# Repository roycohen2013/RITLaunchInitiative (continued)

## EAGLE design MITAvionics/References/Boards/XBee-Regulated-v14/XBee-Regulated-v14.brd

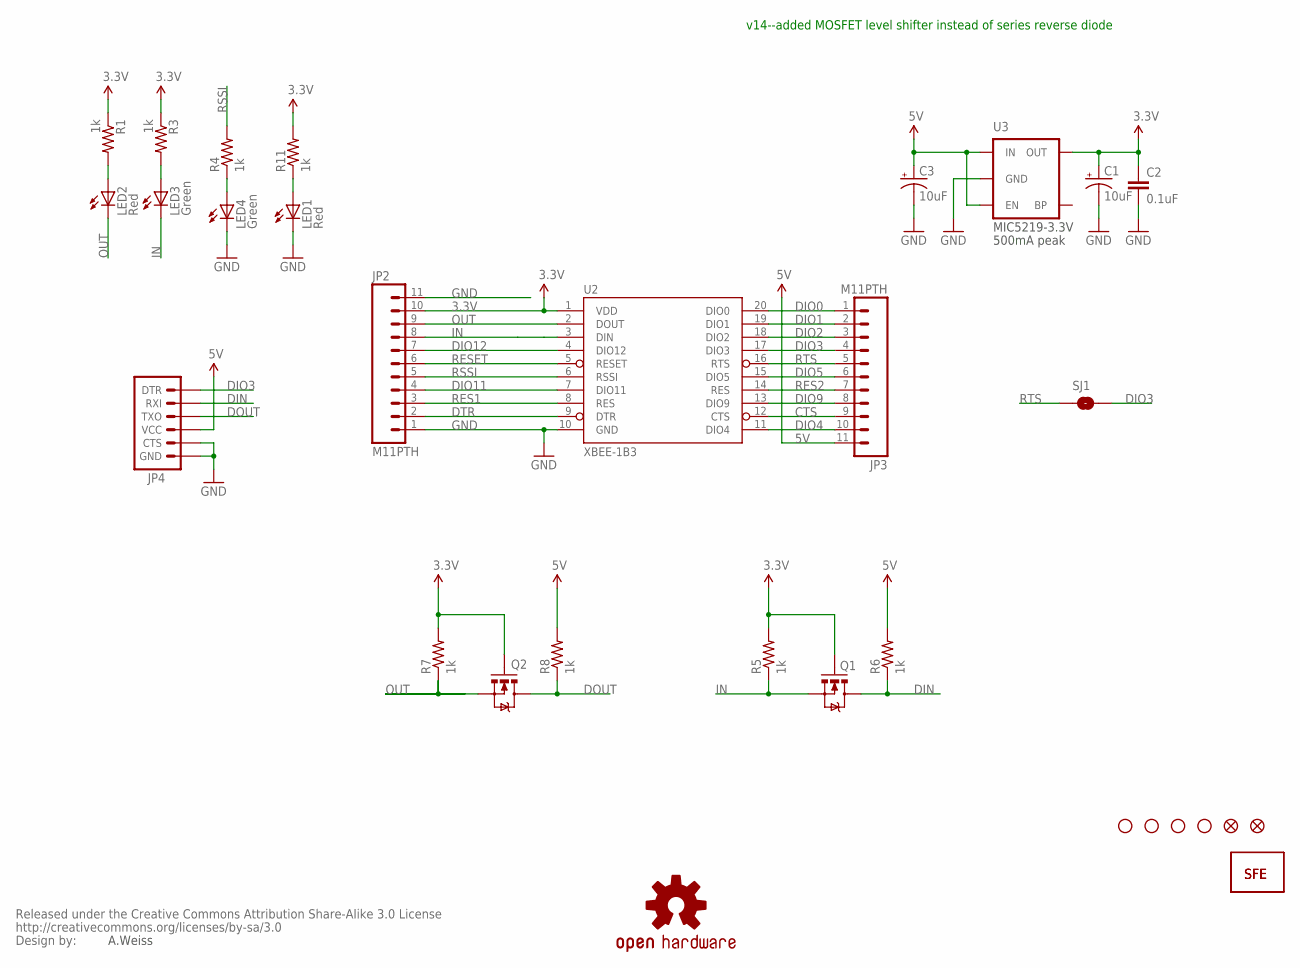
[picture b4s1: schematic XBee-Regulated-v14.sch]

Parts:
C1, C3: 10uF; EIA3216
C2: 0.1uF; 0402-CAP
JP2, JP3: M11PTH; 1X11
JP4: ARDUINO_SERIAL_PROGRAMPTH; 1X06
LED1, LED2: Red; LED-0603
LED3, LED4: Green; LED-0603
Q1, Q2: MOSFET-NCHANNELSMD; SOT23-3
R1, R3, R4, R5, R6, R7, R8, R11: 1k; 0402-RES
SJ1: SOLDERJUMPERNO; SJ_2S-NO
U2: XBEE-1B3; XBEE-SMD
U3: V_REG_LDOSMD; SOT23-5
U$1: LOGO-SFESK; SFE-LOGO-FLAME
U$3: OSHW-LOGOS; OSHW-LOGO-S
U$4: LOGO-SFENEW; SFE-NEW-WEBLOGO
U$5, U$9, U$10, U$11: STAND-OFF
U$7, U$16: FIDUCIAL1X2; FIDUCIAL-1X2
U$8: CREATIVE_COMMONS

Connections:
3.3V: C1.A (+), C2.1, JP2.10, Q1.1 (G), Q2.1 (G), R1.1, R3.1, R5.2, R7.2, R11.2, U2.1 (VDD), U3.5 (OUT)
5V: C3.A (+), JP3.11, JP4.4 (VCC), R6.2, R8.2, U3.1 (IN), U3.3 (EN)
CTS: JP3.9, U2.12 (CTS)
DIN: JP4.2 (RXI), Q1.3 (D), R6.1
DIO0: JP3.1, U2.20 (DIO0)
DIO1: JP3.2, U2.19 (DIO1)
DIO2: JP3.3, U2.18 (DIO2)
DIO3: JP3.4, JP4.1 (DTR), SJ1.2, U2.17 (DIO3)
DIO4: JP3.10, U2.11 (DIO4)
DIO5: JP3.6, U2.15 (DIO5)
DIO9: JP3.8, U2.13 (DIO9)
DIO11: JP2.4, U2.7 (DIO11)
DIO12: JP2.7, U2.4 (DIO12)
DOUT: JP4.3 (TXO), Q2.3 (D), R8.1
DTR: JP2.2, U2.9 (DTR)
GND: C1.C (-), C2.2, C3.C (-), JP2.1, JP2.11, JP4.5 (CTS), JP4.6 (GND), LED1.C, LED4.C, U2.10 (GND), U3.2 (GND)
IN: JP2.8, LED3.C, Q1.2 (S), R5.1, U2.3 (DIN)
unnamed: LED2.A, R1.2
unnamed: LED4.A, R4.1
unnamed: LED3.A, R3.2
unnamed: LED1.A, R11.1
OUT: JP2.9, LED2.C, Q2.2 (S), R7.1, U2.2 (DOUT)
RES1: JP2.3, U2.8 (RES)
RES2: JP3.7, U2.14 (RES)
RESET: JP2.6, U2.5 (RESET)
RSSI: JP2.5, R4.2, U2.6 (RSSI)
RTS: JP3.5, SJ1.1, U2.16 (RTS)

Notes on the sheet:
A.Weiss
v14--added MOSFET level shifter instead of series reverse diode
MIC5219-3.3V
500mA peak

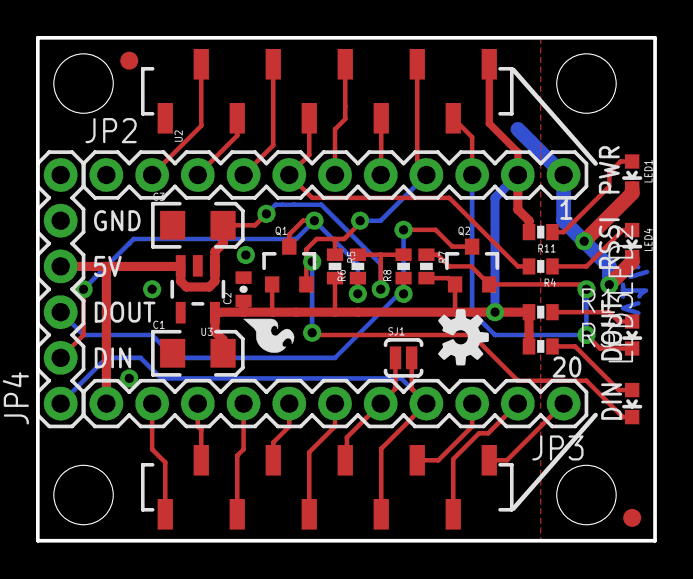
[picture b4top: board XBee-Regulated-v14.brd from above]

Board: 2 copper layers, 34.3 x 27.9 mm, 33 parts (1 on the bottom side), 27 nets.

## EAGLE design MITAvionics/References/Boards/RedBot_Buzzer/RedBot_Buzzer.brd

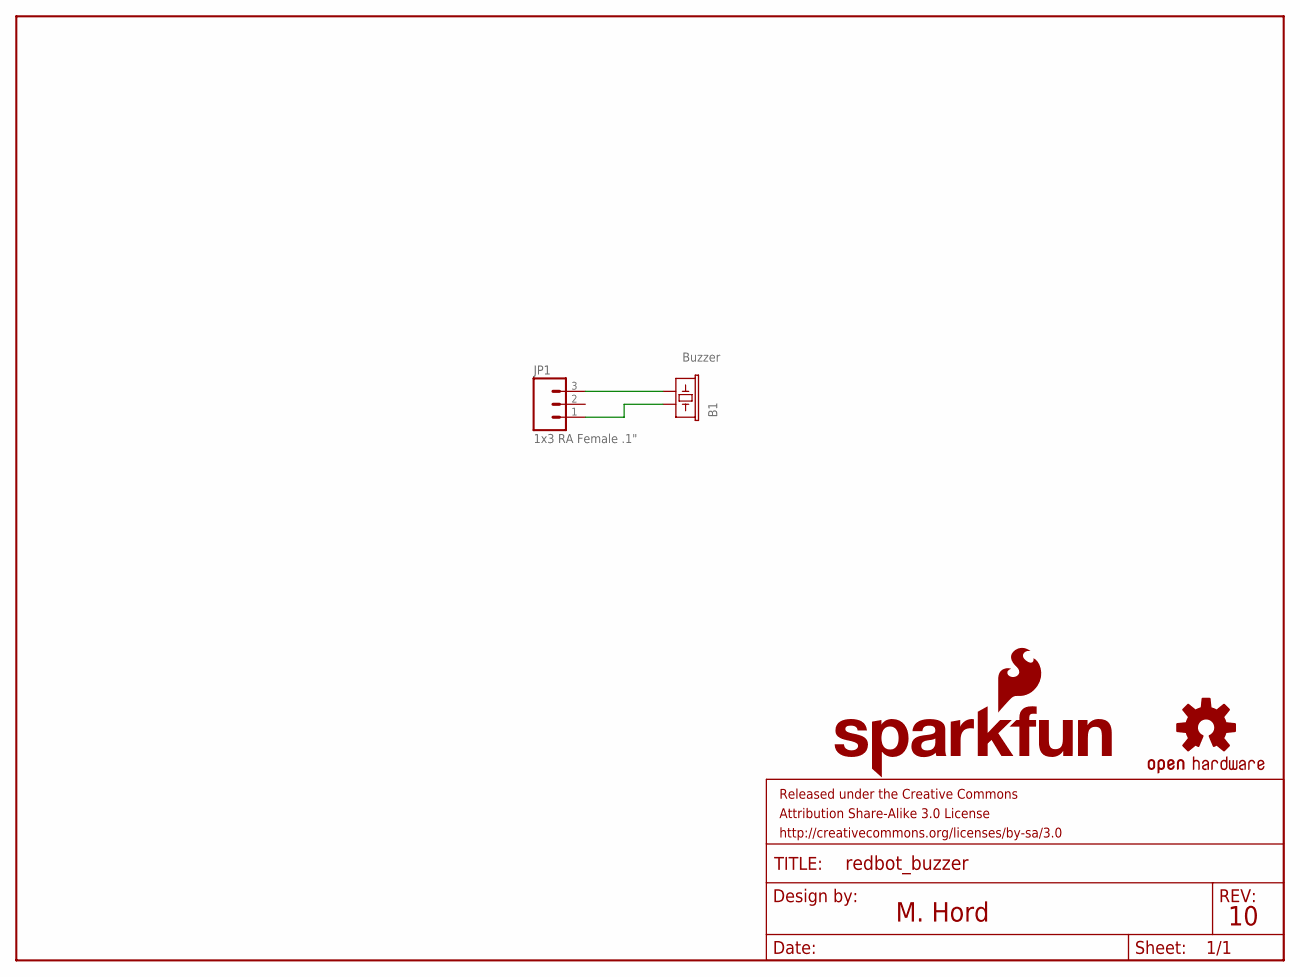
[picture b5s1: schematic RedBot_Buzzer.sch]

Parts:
B1: Buzzer; BUZZER-CCV
FRAME1: FRAME-LETTER; CREATIVE_COMMONS
JP1: 1x3 RA Female .1"; 1X03_SMD_RA_FEMALE
LOGO1: OSHW-LOGOS; OSHW-LOGO-S
LOGO2: SFE_LOGO_NAME_FLAME.1_INCH; SFE_LOGO_NAME_FLAME_.1

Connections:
unnamed: B1.+ (1), JP1.1
unnamed: B1.- (2), JP1.3

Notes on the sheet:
M. Hord

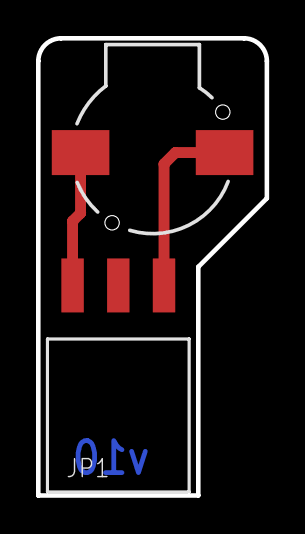
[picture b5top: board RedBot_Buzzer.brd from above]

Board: 2 copper layers, 12.7 x 25.4 mm, 5 parts (2 on the bottom side), 2 nets.

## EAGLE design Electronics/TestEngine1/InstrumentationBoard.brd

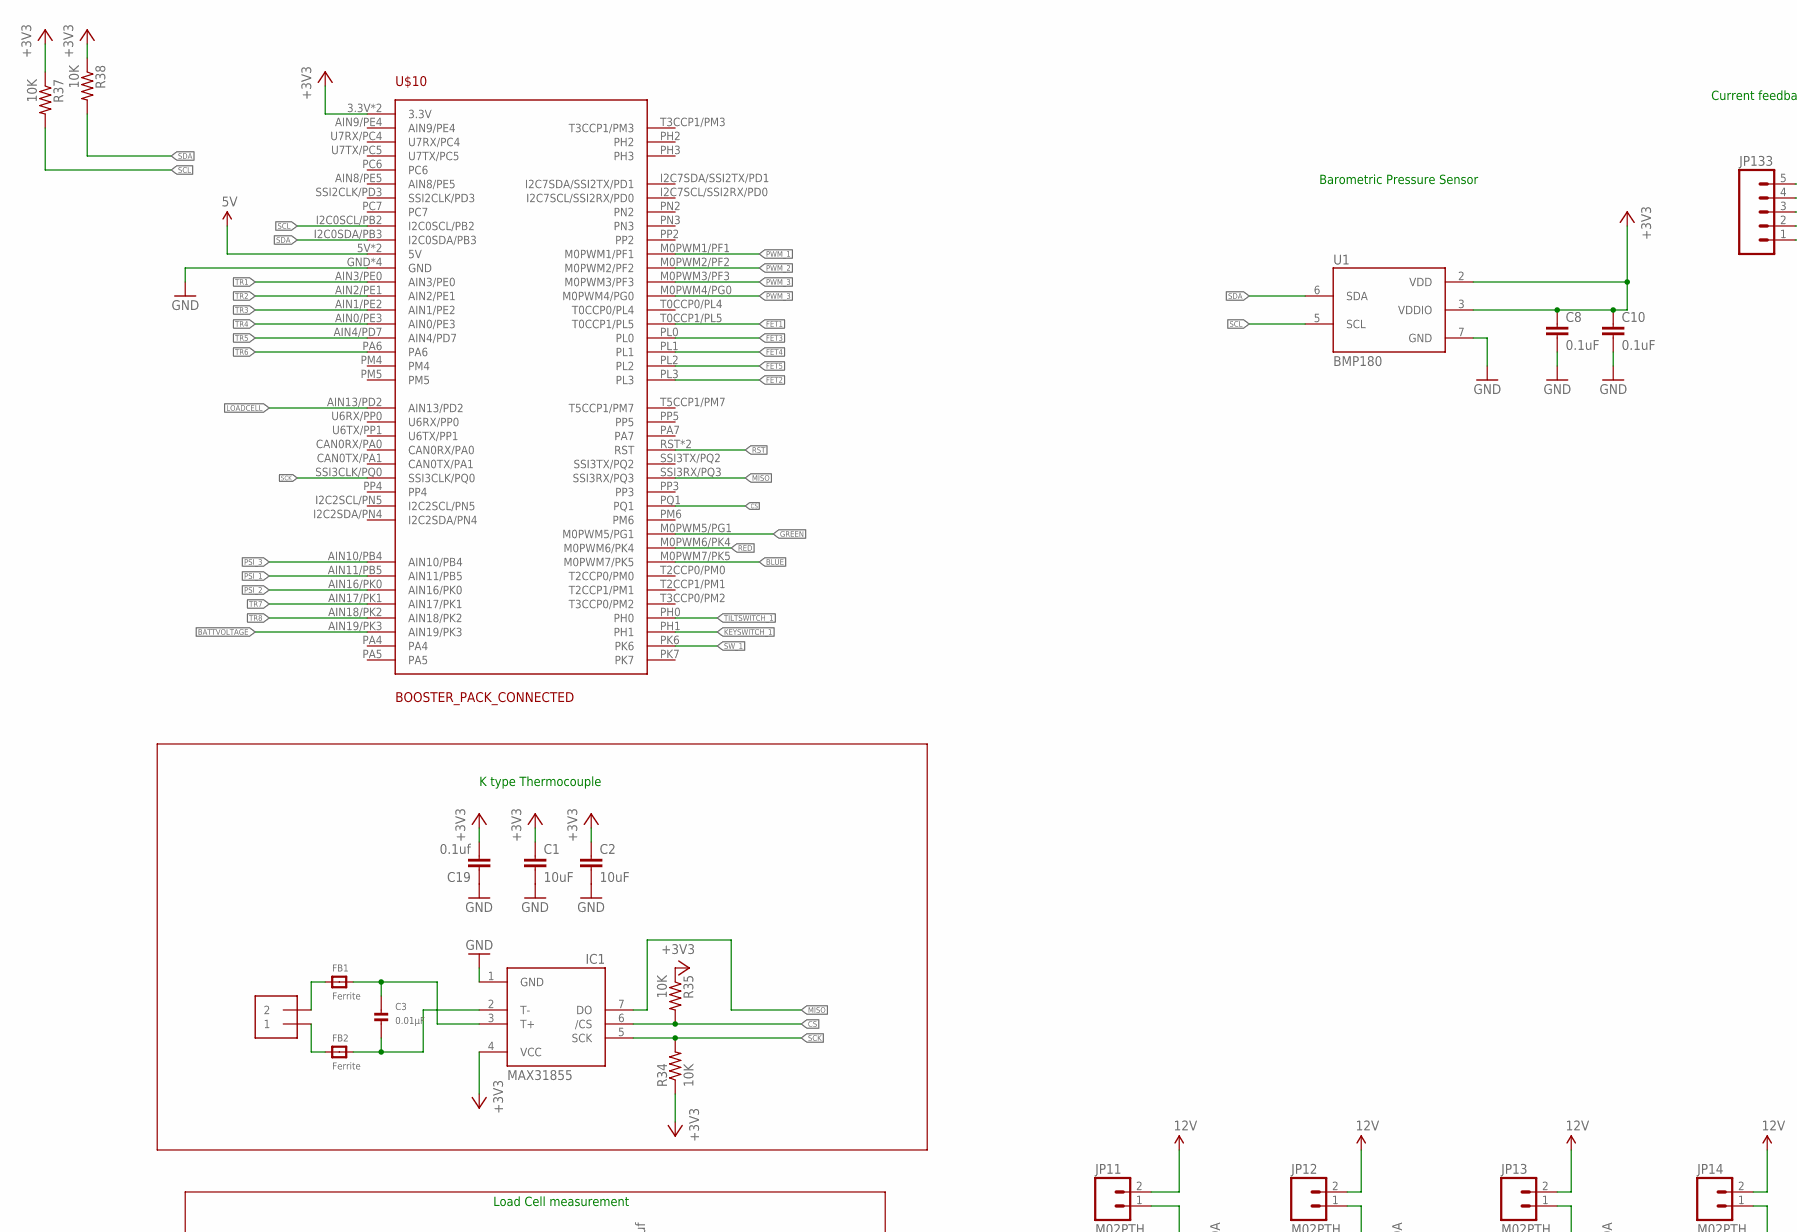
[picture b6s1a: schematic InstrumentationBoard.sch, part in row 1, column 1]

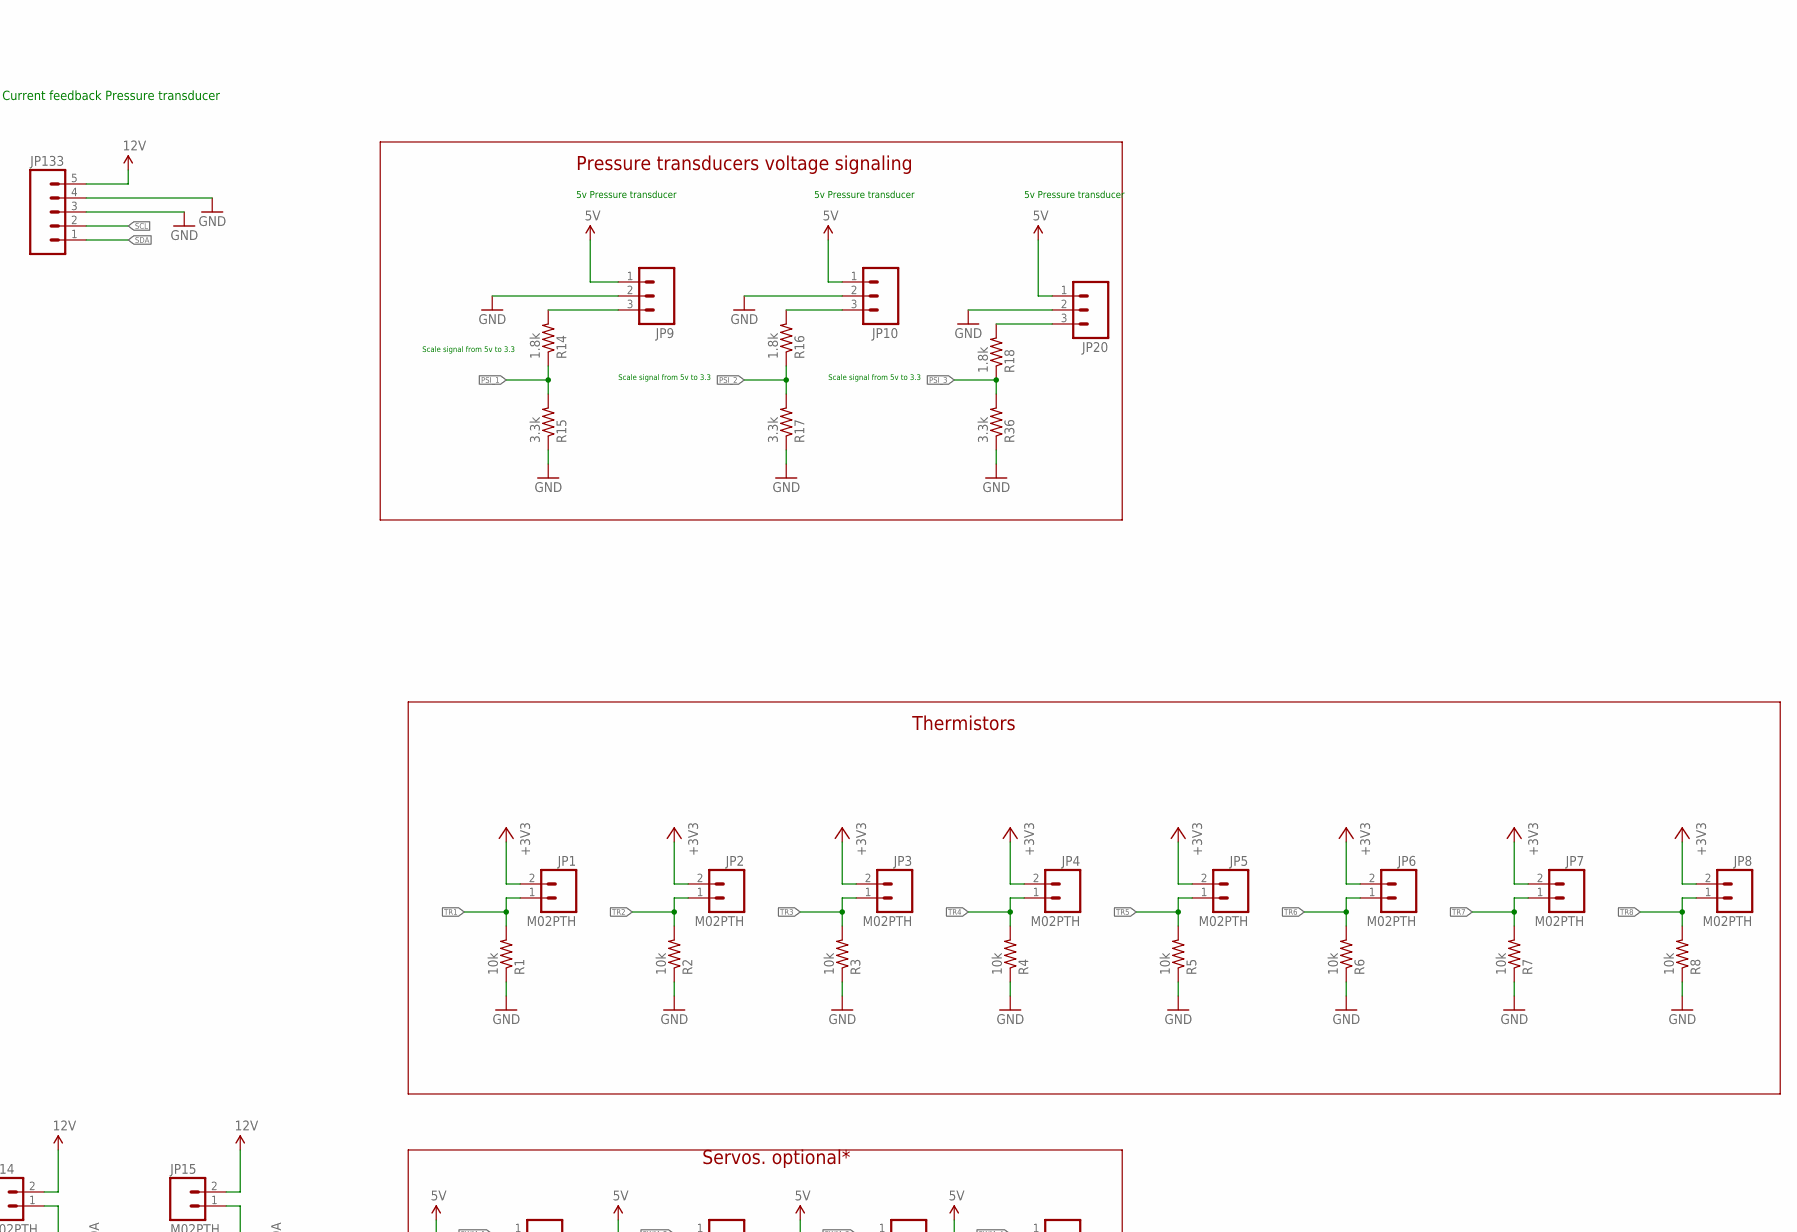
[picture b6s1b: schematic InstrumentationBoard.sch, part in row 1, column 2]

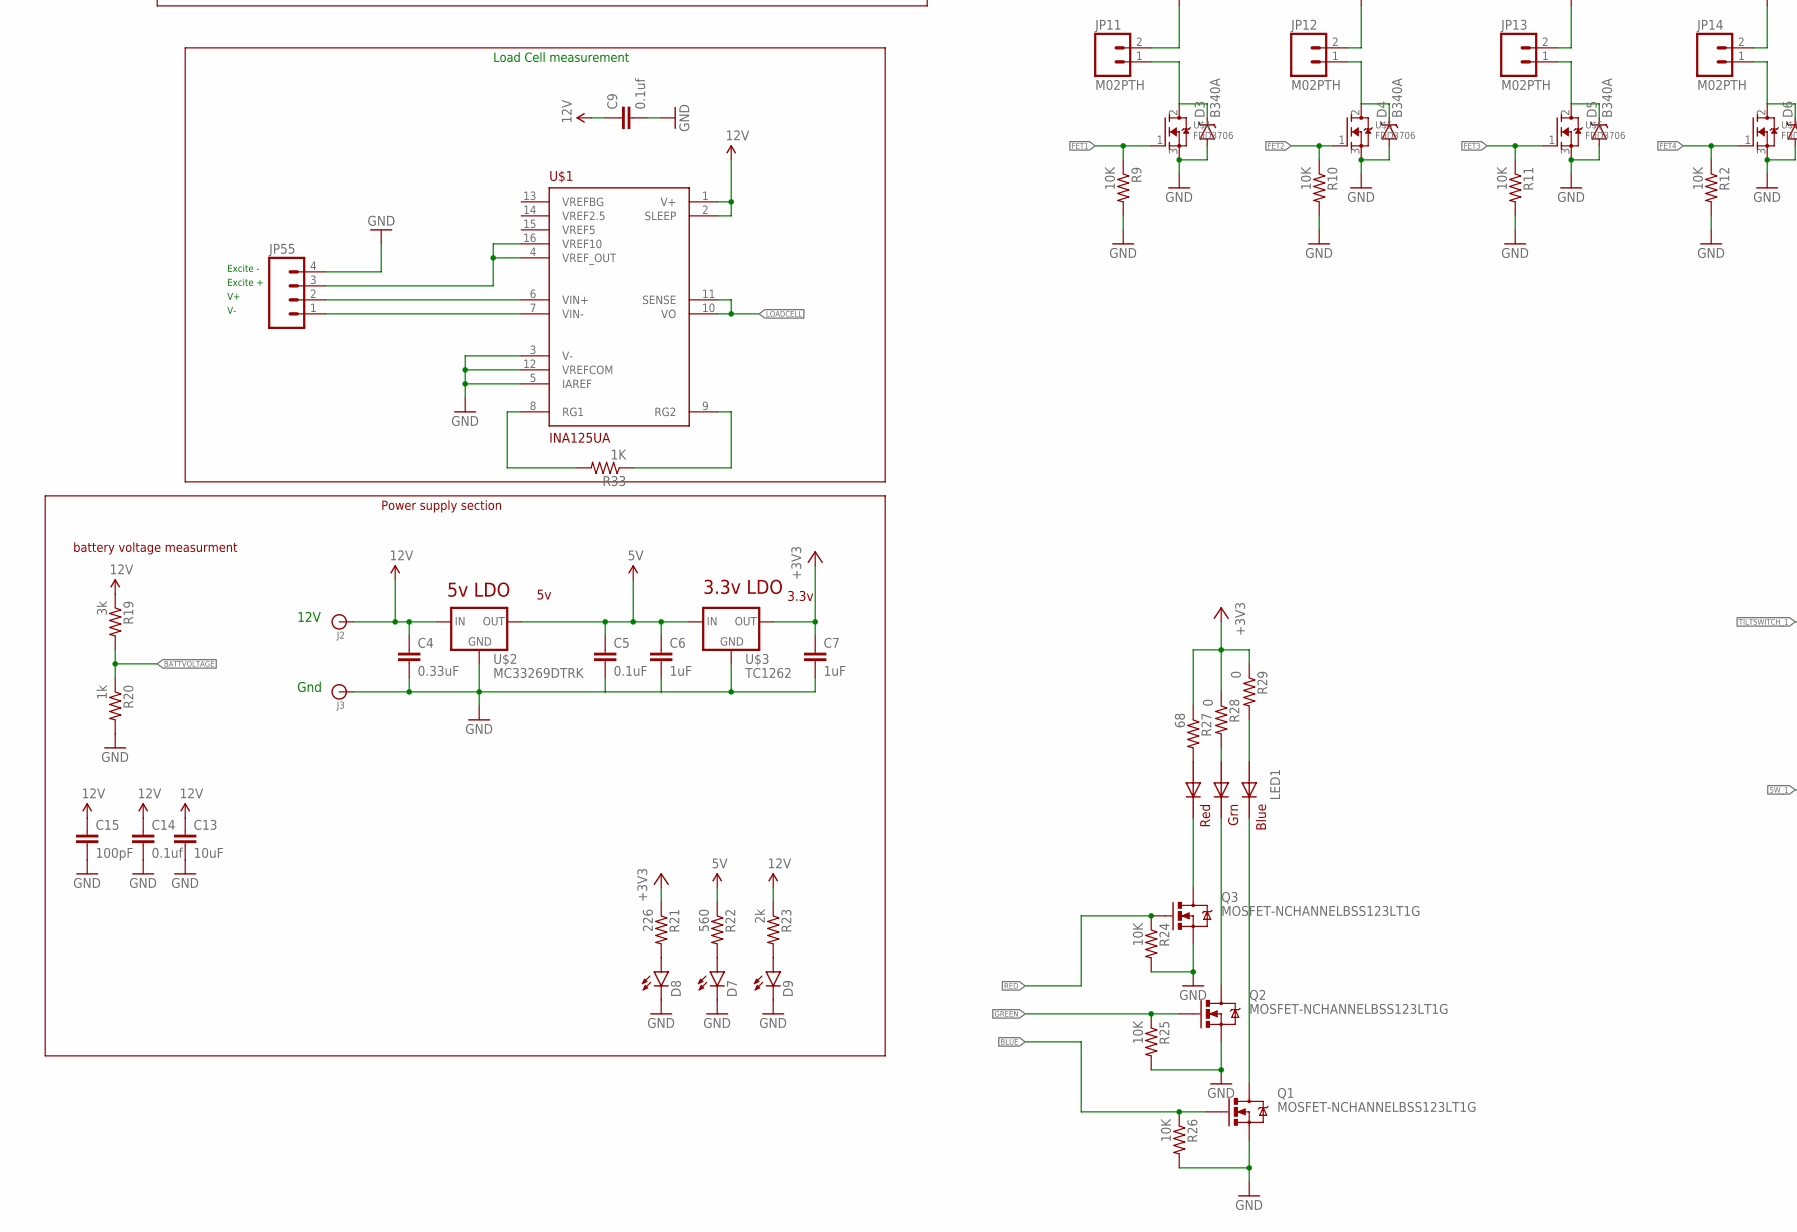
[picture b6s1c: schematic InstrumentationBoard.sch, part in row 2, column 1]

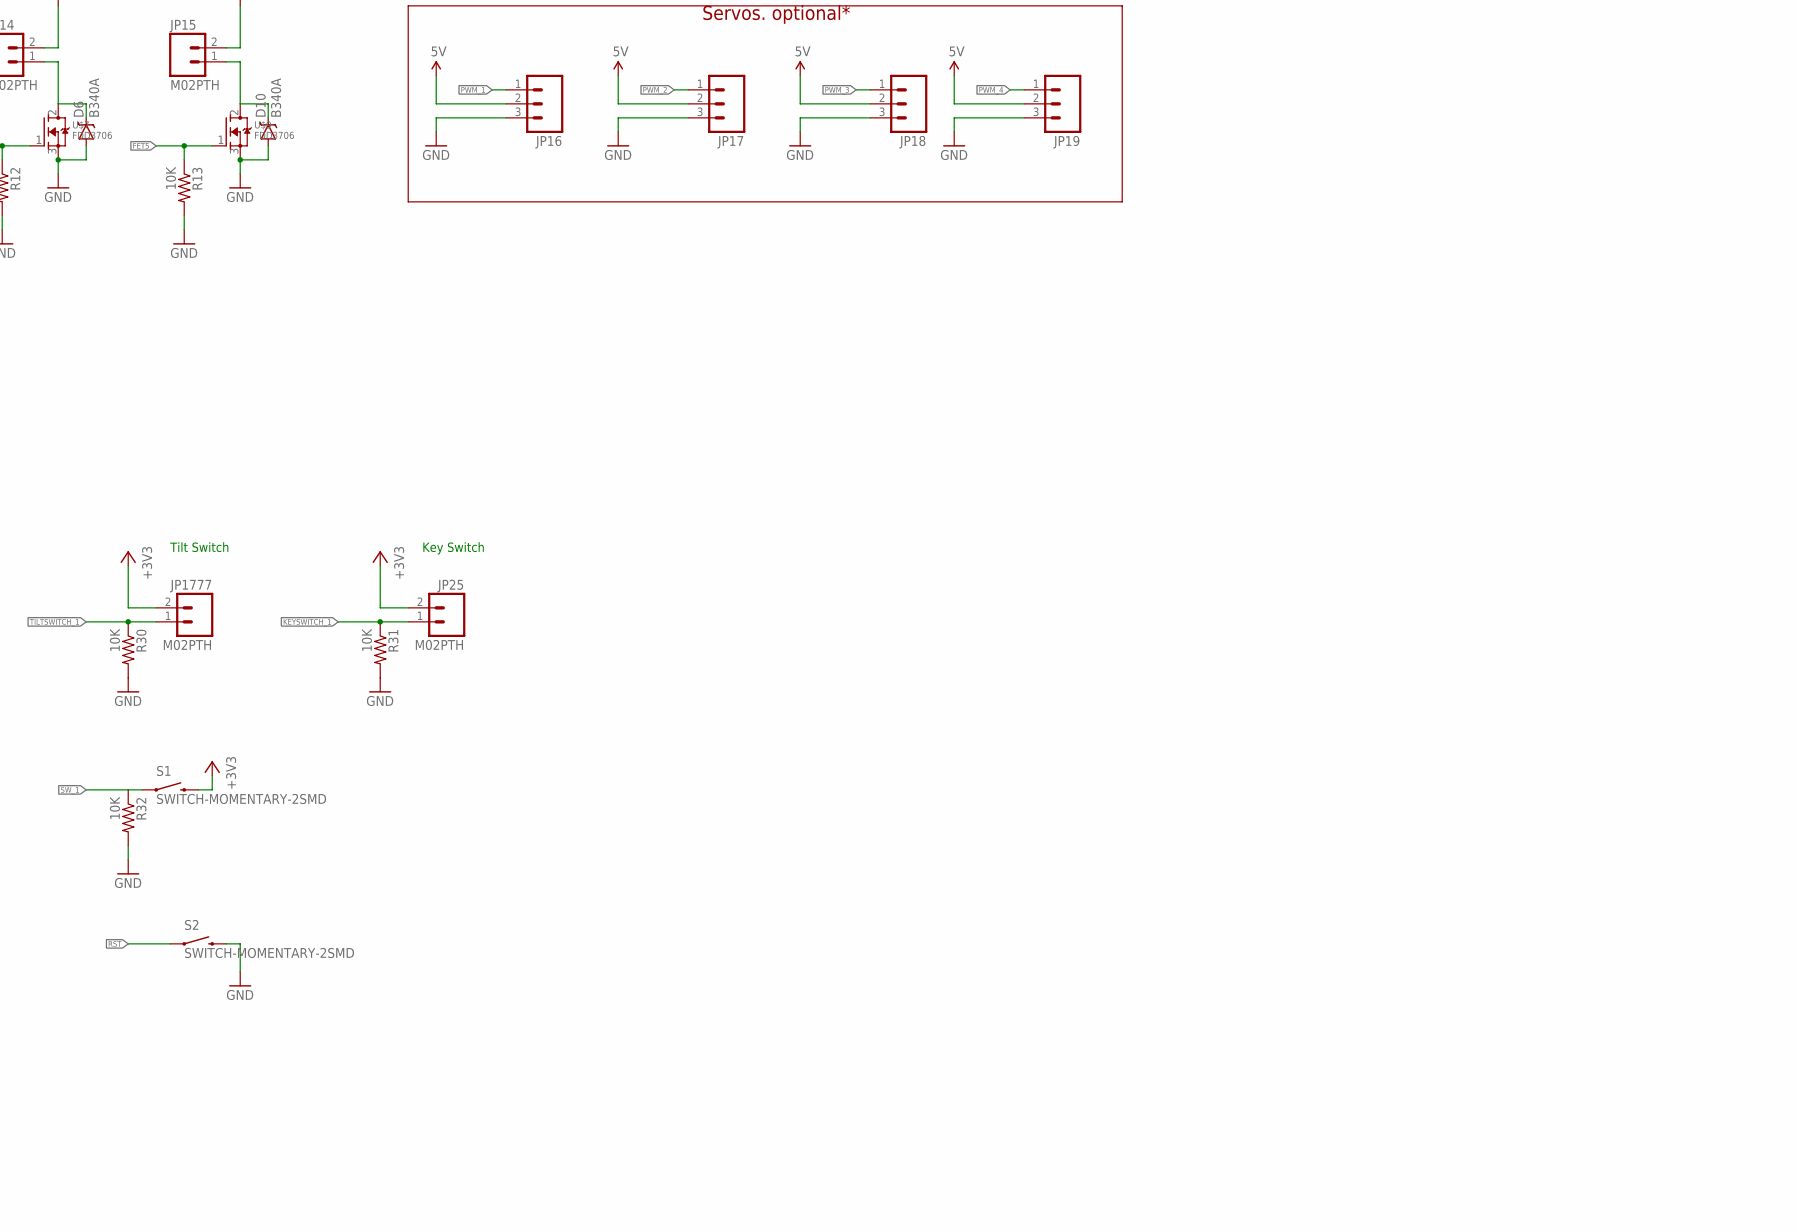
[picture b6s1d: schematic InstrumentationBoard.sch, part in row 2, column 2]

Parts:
C1, C2: 10uF; 0805
C3: 0.01µF; _0805; DIGIKEY 490-1664-1-ND
C4: 0.33uF; 0805
C5, C8, C10: 0.1uF; 0805
C6, C7: 1uF; 0805
C9, C14, C19: 0.1uf; 0805
C13: 10uF; 0805; DIGIKEY 490-3886-1-ND
C15: 100pF; 0805
D3, D4, D5, D6, D10: B340A; SMA-DIODE; DIGIKEY SS110-TPCT-ND
D7, D8, D9: LED1206; LED-1206; DIGIKEY 160-1405-1-ND
FB1, FB2: Ferrite; _0805; DIGIKEY 732-1609-1-ND
IC1: MAX31855; SO08
J1: 1X2-3.5MM
J2, J3: BANANA_CONN
JP1, JP2, JP3, JP4, JP5, JP6, JP7, JP8, JP11, JP12, JP13, JP14, JP15, JP25, JP1777: M02PTH; 1X02
JP9, JP10, JP16, JP17, JP18, JP19, JP20: M03PTH; 1X03
JP55: M04PTH; 1X04
JP133: M05PTH; 1X05
LED1: RGBLED5050; DIGIKEY 1516-1131-1-ND
Q1, Q2, Q3: MOSFET-NCHANNELBSS123LT1G; SOT23-3
R1, R2, R3, R4, R5, R6, R7, R8: 10k; 0805
R9, R10, R11, R12, R13, R24, R25, R26, R30, R31, R32, R34, R35, R37, R38: 10K; 0805
R14, R16, R18: 1.8k; 0805; DIGIKEY RMCF0805FT1K80CT-ND
R15, R17, R36: 3.3k; 0805; DIGIKEY RHM3.30KCHCT-ND
R19: 3k; 0805
R20: 1k; 0805
R21: 226; 0805; DIGIKEY P226CCT-ND
R22: 560; 0805; DIGIKEY P560CCT-ND
R23: 2k; 0805; DIGIKEY P2.00KCCT-ND
R27: 68; 0805
R28, R29: 0; 0805
R33: 1K; 0805
S1, S2: SWITCH-MOMENTARY-2SMD; TACTILE-SWITCH-SMD
U1: BMP180
U$1: INA125UA; SO16
U$2: MC33269DTRK; TO-252; DIGIKEY MC33269DTRK-5.0GOSCT-ND
U$3: TC1262; SOT223; DIGIKEY TC1262-3.3VDBCT-ND
U$4, U$5, U$6, U$7, U$9: FDD3706; TO-252
U$10: BOOSTER_PACK_CONNECTED; TI_CONNECTED_BOOSTER

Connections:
5V: C5.1, C6.1, JP9.1, JP10.1, JP16.2, JP17.2, JP18.2, JP19.2, JP20.1, R22.1, U$2.2 (OUT), U$3.1 (IN), U$10.5V, U$10.5V1 (5V)
12V: C4.1, C9.1, C13.1, C14.1, C15.1, J2.P$1, JP11.2, JP12.2, JP13.2, JP14.2, JP15.2, JP133.5, R19.1, R23.1, U$1.1 (V+), U$1.2 (SLEEP), U$2.3 (IN)
+3V3: C1.1, C2.1, C7.1, C8.1, C10.1, C19.2, IC1.4 (VCC), JP1.2, JP2.2, JP3.2, JP4.2, JP5.2, JP6.2, JP7.2, JP8.2, JP25.2, JP1777.2, R21.1, R27.1, R28.1, R29.1, R34.1, R35.1, R37.1, R38.1, S1.3 (2), U1.2 (VDD), U1.3 (VDDIO), U$3.3 (OUT), U$10.3.3V, U$10.3.3V1 (3.3V)
BATTVOLTAGE: R19.2, R20.1, U$10.AIN19/PK3
BLUE: Q1.1 (G), R26.1, U$10.M0PWM7/PK5
CS: IC1.6 (/CS), R35.2, U$10.PQ1
EXCITE+: JP55.3, U$1.4 (VREF_OUT), U$1.16 (VREF10)
FET1: R9.1, U$4.1 (G), U$10.T0CCP1/PL5
FET2: R10.1, U$5.1 (G), U$10.PL3
FET3: R11.1, U$6.1 (G), U$10.PL0
FET4: R12.1, U$7.1 (G), U$10.PL1
FET5: R13.1, U$9.1 (G), U$10.PL2
GND: C1.2, C2.2, C4.2, C5.2, C6.2, C7.2, C8.2, C9.2, C10.2, C13.2, C14.2, C15.2, C19.1, D3.A, D4.A, D5.A, D6.A, D7.C, D8.C, D9.C, D10.A, IC1.1 (GND), J3.P$1, JP9.2, JP10.2, JP16.3, JP17.3, JP18.3, JP19.3, JP20.2, JP55.4, JP133.3, JP133.4, Q1.2 (S), Q2.2 (S), Q3.2 (S), R1.1, R2.1, R3.1, R4.1, R5.1, R6.1, R7.1, R8.1, R9.2, R10.2, R11.2, R12.2, R13.2, R15.1, R17.1, R20.2, R24.2, R25.2, R26.2, R30.2, R31.2, R32.2, R36.1, S2.3 (2), U1.7 (GND), U$1.3 (V-), U$1.5 (IAREF), U$1.12 (VREFCOM), U$2.1 (GND), U$3.2 (GND), U$4.3 (S), U$5.3 (S), U$6.3 (S), U$7.3 (S), U$9.3 (S), U$10.GND, U$10.GND1 (GND), U$10.GND2 (GND), U$10.GND3 (GND)
GREEN: Q2.1 (G), R25.1, U$10.M0PWM5/PG1
KEYSWITCH_1: JP25.1, R31.1, U$10.PH1
LOADCELL: U$1.10 (VO), U$1.11 (SENSE), U$10.AIN13/PD2
MISO: IC1.7 (DO), U$10.SSI3RX/PQ3
unnamed: JP9.3, R14.2
unnamed: LED1.5 (RED_C), Q3.3 (D)
unnamed: LED1.6 (GREEN_C), Q2.3 (D)
unnamed: LED1.4 (BLUE_C), Q1.3 (D)
unnamed: LED1.2 (RED_A), R27.2
unnamed: LED1.1 (GREEN_A), R28.2
unnamed: R33.2, U$1.8 (RG1)
unnamed: R33.1, U$1.9 (RG2)
unnamed: LED1.3 (BLUE_A), R29.2
unnamed: D6.C, JP14.1, U$7.2 (D)
unnamed: D3.C, JP11.1, U$4.2 (D)
unnamed: D4.C, JP12.1, U$5.2 (D)
unnamed: JP10.3, R16.2
unnamed: D5.C, JP13.1, U$6.2 (D)
unnamed: D7.A, R22.2
unnamed: D8.A, R21.2
unnamed: D9.A, R23.2
unnamed: D10.C, JP15.1, U$9.2 (D)
unnamed: JP20.3, R18.2
PSI_1: R14.1, R15.2, U$10.AIN11/PB5
PSI_2: R16.1, R17.2, U$10.AIN16/PK0
PSI_3: R18.1, R36.2, U$10.AIN10/PB4
PWM_1: JP16.1, U$10.M0PWM1/PF1
PWM_2: JP17.1, U$10.M0PWM2/PF2
PWM_3: JP18.1, U$10.M0PWM3/PF3
PWM_4: JP19.1, U$10.M0PWM4/PG0
RED: Q3.1 (G), R24.1, U$10.M0PWM6/PK4
RST: S2.1, U$10.RST, U$10.RST1 (RST)
SCK: IC1.5 (SCK), R34.2, U$10.SSI3CLK/PQ0
SCL: JP133.2, R37.2, U1.5 (SCL), U$10.I2C0SCL/PB2
SDA: JP133.1, R38.2, U1.6 (SDA), U$10.I2C0SDA/PB3
SW_1: R32.1, S1.1, U$10.PK6
T+: C3.1, FB1.2, IC1.3 (T+)
T-: C3.2, FB2.2, IC1.2 (T-)
TILTSWITCH_1: JP1777.1, R30.1, U$10.PH0
TR1: JP1.1, R1.2, U$10.AIN3/PE0
TR2: JP2.1, R2.2, U$10.AIN2/PE1
TR3: JP3.1, R3.2, U$10.AIN1/PE2
TR4: JP4.1, R4.2, U$10.AIN0/PE3
TR5: JP5.1, R5.2, U$10.AIN4/PD7
TR6: JP6.1, R6.2, U$10.PA6
TR7: JP7.1, R7.2, U$10.AIN17/PK1
TR8: JP8.1, R8.2, U$10.AIN18/PK2
TT+: FB1.1, J1.2
TT-: FB2.1, J1.1
VIN+: JP55.2, U$1.6 (VIN+)
VIN-: JP55.1, U$1.7 (VIN-)

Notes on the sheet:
12V
Gnd
Excite -
Excite +
5v Pressure transducer
Current feedback Pressure transducer
Barometric Pressure Sensor
Scale signal from 5v to 3.3
K type Thermocouple
Load Cell measurement
Tilt Switch
Thermistors
Pressure transducers voltage signaling
Servos. optional*
5v LDO
3.3v LDO
battery voltage measurment
Power supply section
Key Switch

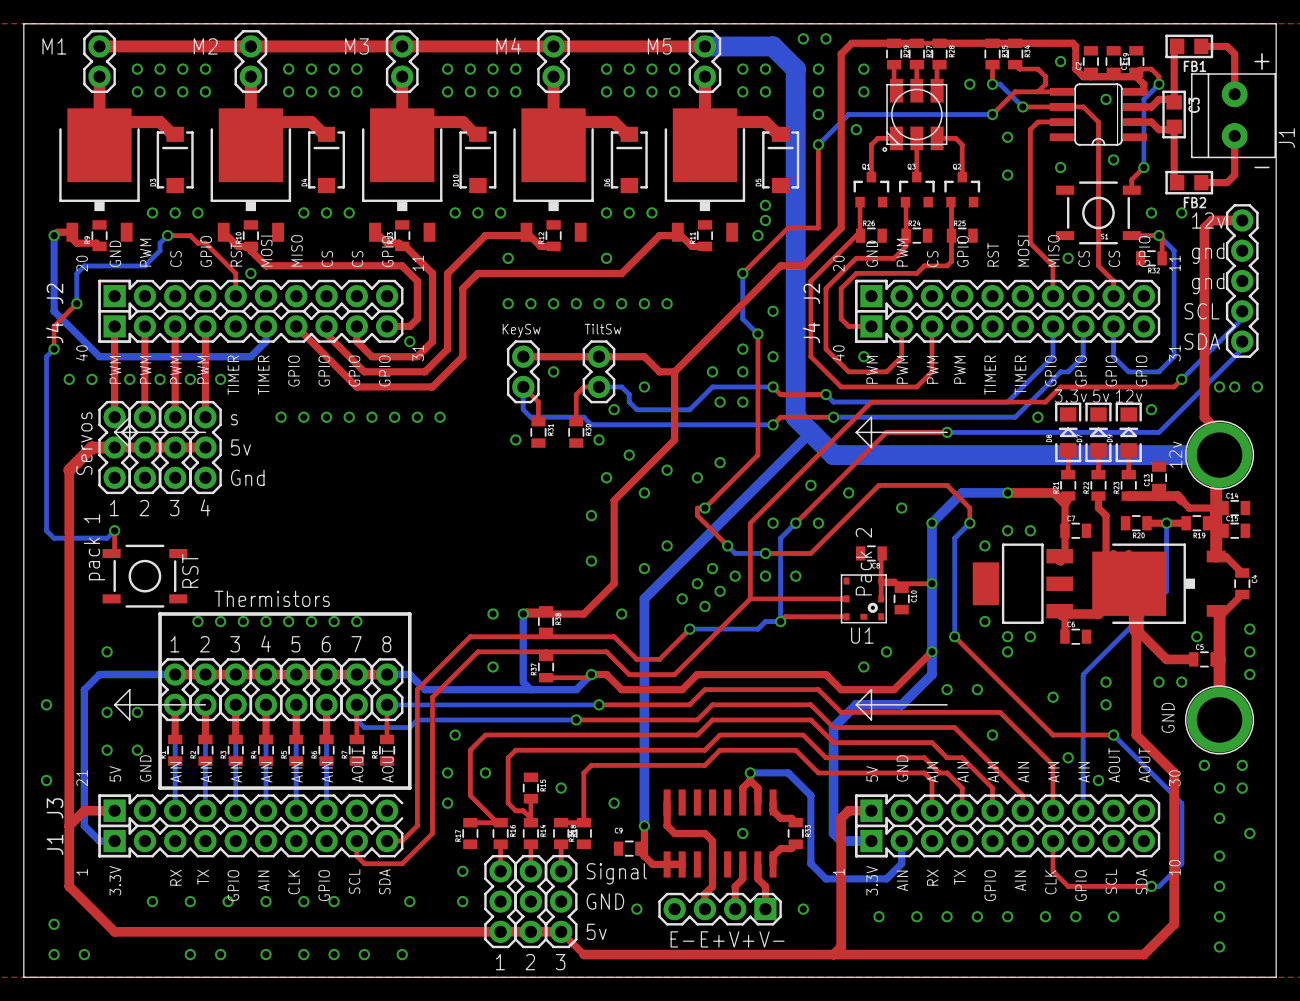
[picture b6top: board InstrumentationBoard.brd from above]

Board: 2 copper layers, 105.1 x 80.0 mm, 107 parts (1 on the bottom side), 64 nets.

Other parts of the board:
U$8: RITLAUNCH_LOGO

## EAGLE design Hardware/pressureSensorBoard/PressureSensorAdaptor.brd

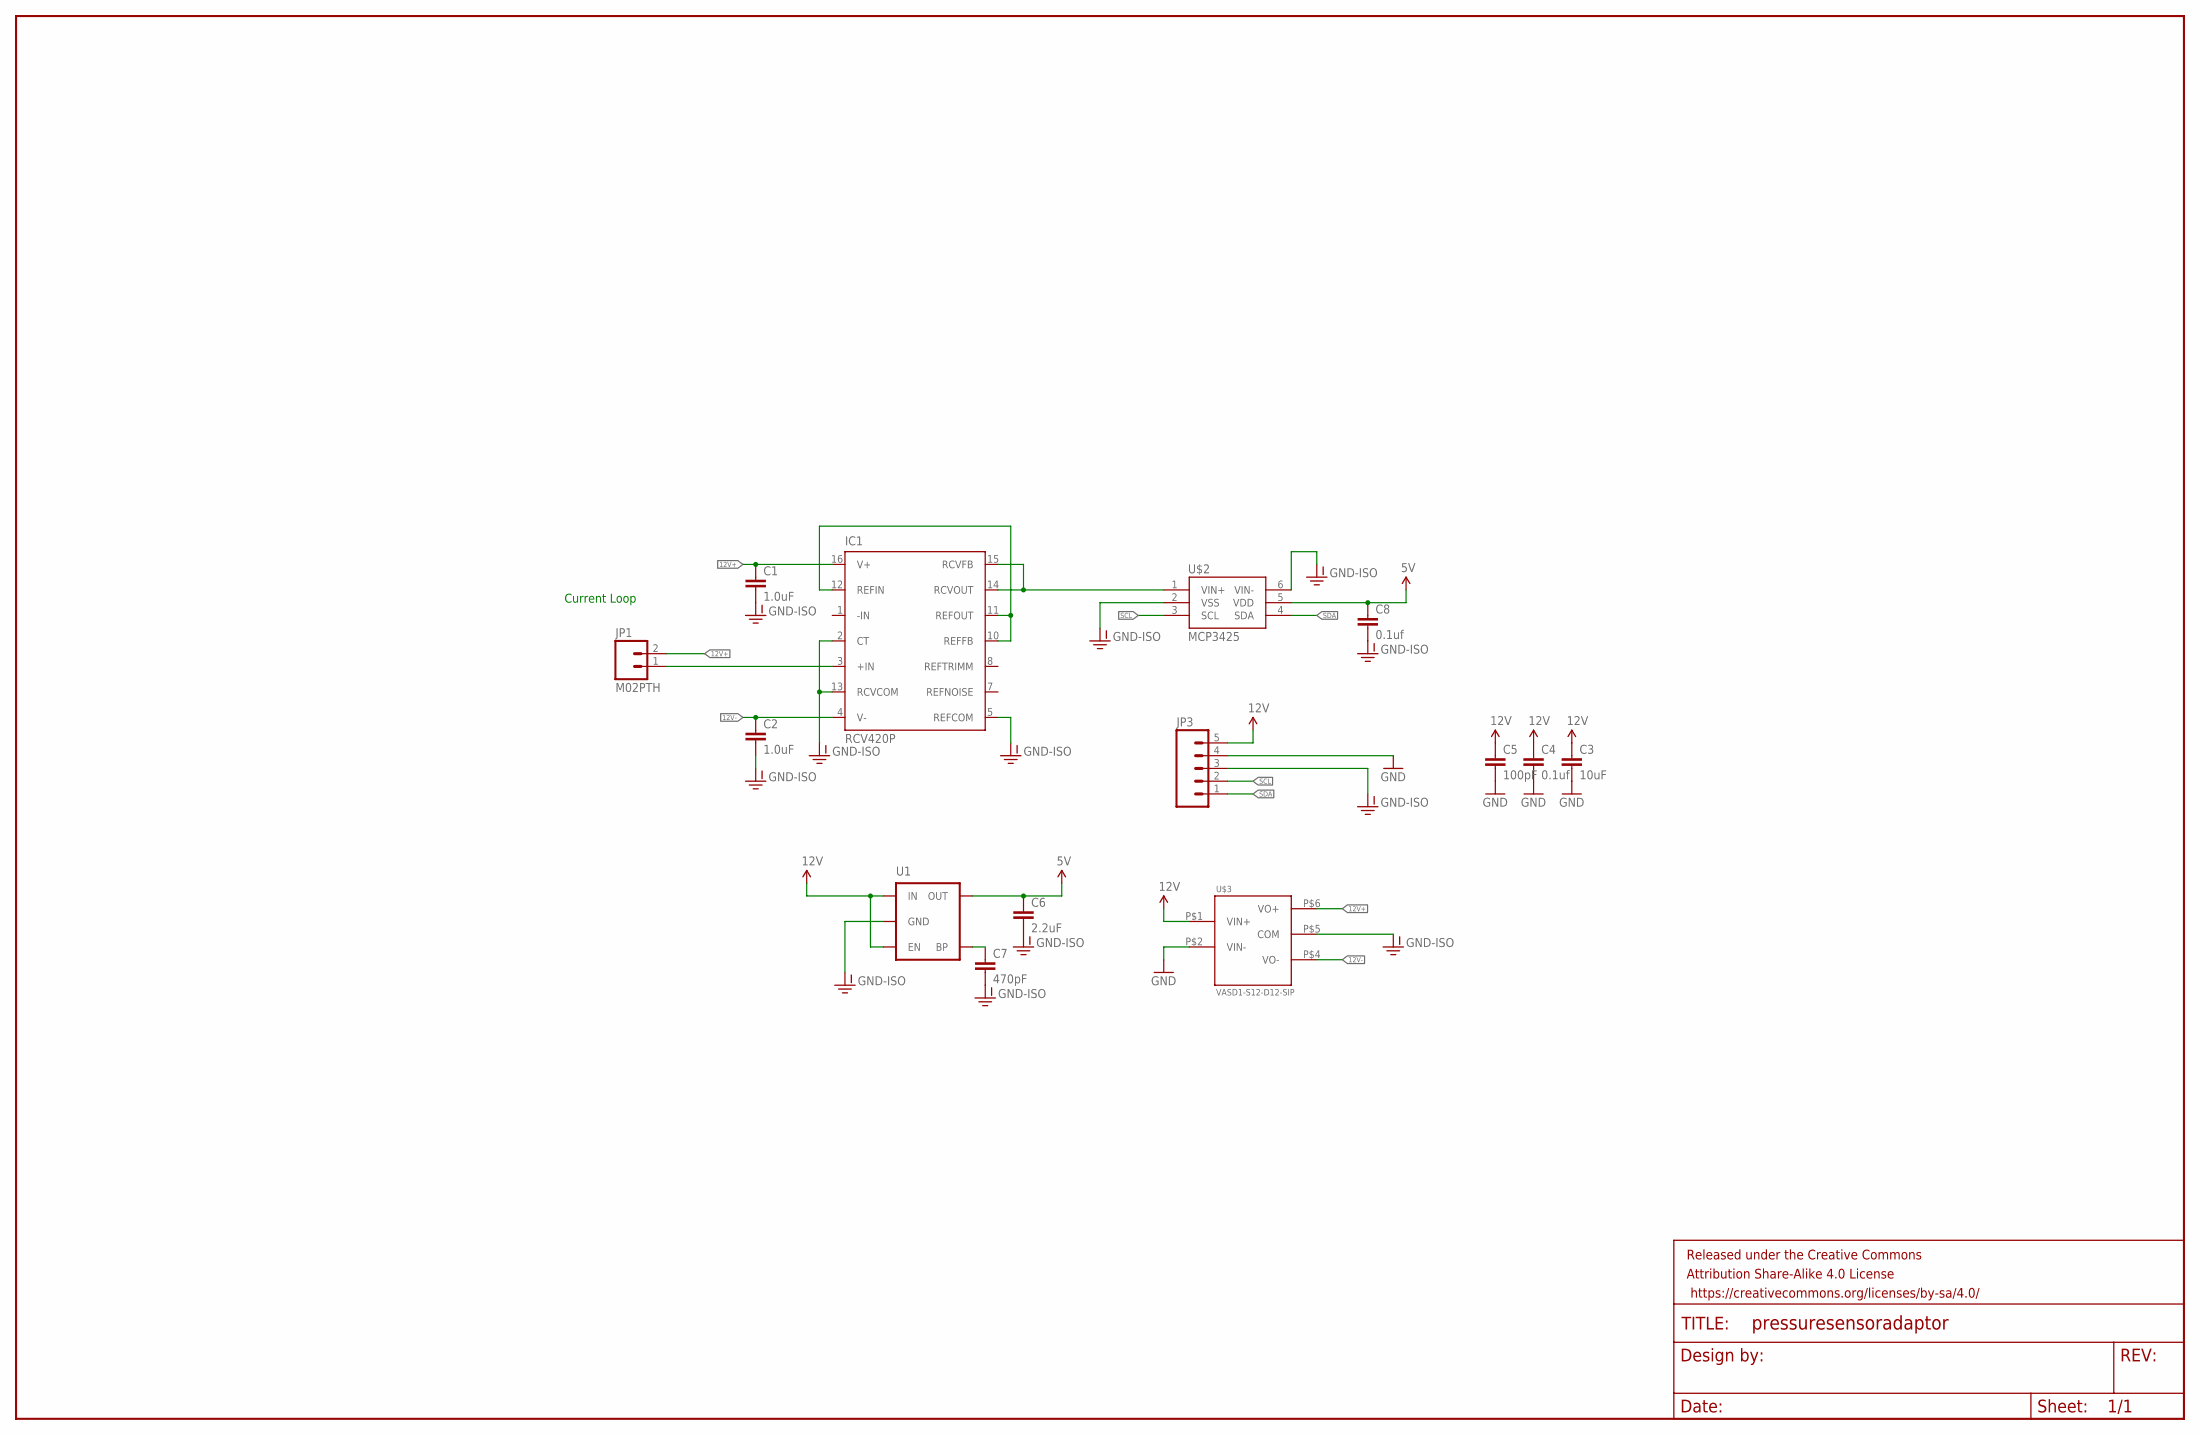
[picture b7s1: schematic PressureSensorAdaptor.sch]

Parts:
C1, C2: 1.0uF; 0805
C3: 10uF; 0805; DIGIKEY 490-3886-1-ND
C4, C8: 0.1uf; 0805
C5: 100pF; 0805
C6: 2.2uF; 0805
C7: 470pF; 0603-CAP
FRAME1: FRAME-LEDGER; CREATIVE_COMMONS
IC1: RCV420P; DIL16
JP1: M02PTH; 1X02
JP3: M05PTH; 1X05
U1: MIC52055V; SOT23-5
U$2: MCP3425; SOT23-6
U$3: VASD1-S12-D12-SIP

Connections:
5V: C6.1, C8.1, U1.5 (OUT), U$2.5 (VDD)
12V: C3.1, C4.1, C5.1, JP3.5, U1.1 (IN), U1.3 (EN), U$3.P$1 (VIN+)
12V+: C1.1, IC1.16 (V+), JP1.2, U$3.P$6 (VO+)
12V-: C2.1, IC1.4 (V-), U$3.P$4 (VO-)
GND: C3.2, C4.2, C5.2, JP3.4, U$3.P$2 (VIN-)
GND-ISO: C1.2, C2.2, C6.2, C7.2, C8.2, IC1.2 (CT), IC1.5 (REFCOM), IC1.13 (RCVCOM), JP3.3, U1.2 (GND), U$2.2 (VSS), U$2.6 (VIN-), U$3.P$5 (COM)
unnamed: IC1.10 (REFFB), IC1.11 (REFOUT), IC1.12 (REFIN)
unnamed: IC1.3 (+IN), JP1.1
unnamed: C7.1, U1.4 (BP)
SCL: JP3.2, U$2.3 (SCL)
SDA: JP3.1, U$2.4 (SDA)
VOUT: IC1.14 (RCVOUT), IC1.15 (RCVFB), U$2.1 (VIN+)

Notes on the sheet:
Current Loop

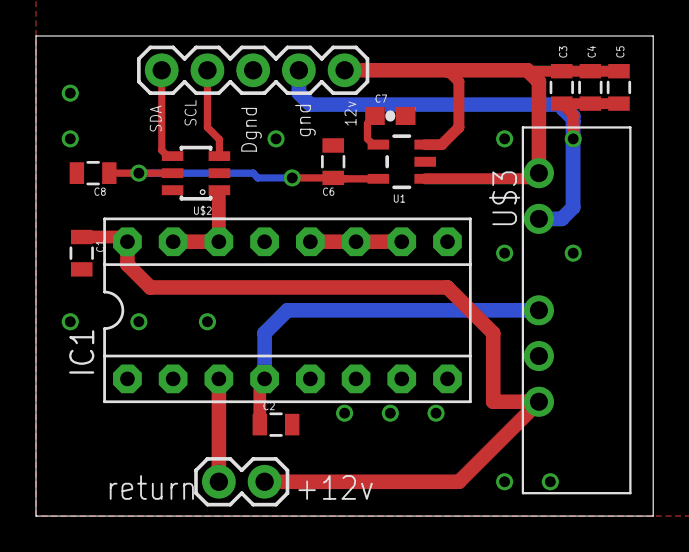
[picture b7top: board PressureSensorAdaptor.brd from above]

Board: 2 copper layers, 34.3 x 26.7 mm, 16 parts (0 on the bottom side), 12 nets.

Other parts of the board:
U$1: RITLAUNCH_LOGO_SMALLB

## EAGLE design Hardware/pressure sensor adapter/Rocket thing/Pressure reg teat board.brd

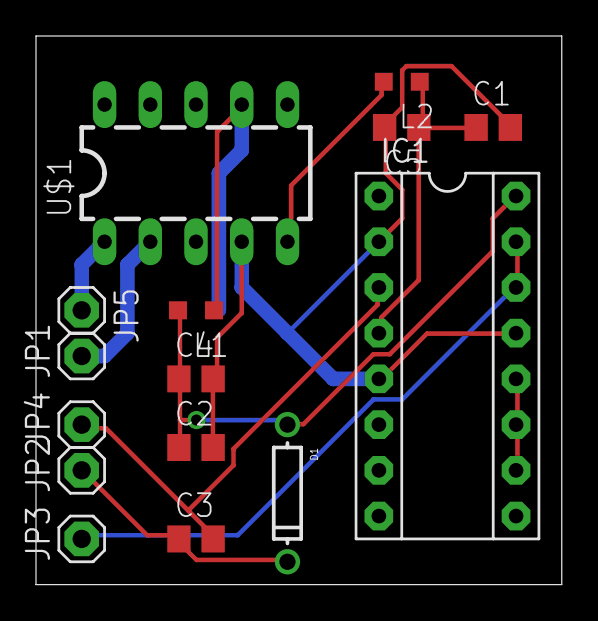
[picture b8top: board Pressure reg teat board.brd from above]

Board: 2 copper layers, 29.2 x 30.5 mm, 15 parts (0 on the bottom side), 11 nets.

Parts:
C1, C2: .22uF; C0805
C3: .01uF; C0805
C4, C5: 1uF; C0805
D1: DO-1N4148
IC1: RCV420P; DIL16
JP1: Vin+; 1X01
JP2: PSV+; 1X01
JP3: Vout; 1X01
JP4: PSIo; 1X01
JP5: Vin-; 1X01
L1, L2: 220uH; L2012C
U$1: NTA1215MC-DC_CONVERTER-SMT

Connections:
GND: C1.2, C2.2, C4.2, C5.2, IC1.2, IC1.5, IC1.13, U$1.4
unnamed: IC1.10, IC1.11, IC1.12
unnamed: C1.1, C5.1, IC1.4, L2.1
unnamed: IC1.14, IC1.15, JP3.1
unnamed: C2.1, C4.1, D1.A, IC1.16, L1.2
unnamed: C3.2, IC1.3, JP4.1
unnamed: L2.2, U$1.5
unnamed: L1.1, U$1.7
unnamed: JP5.1, U$1.1
unnamed: JP1.1, U$1.2
PSV+: C3.1, D1.C, JP2.1
